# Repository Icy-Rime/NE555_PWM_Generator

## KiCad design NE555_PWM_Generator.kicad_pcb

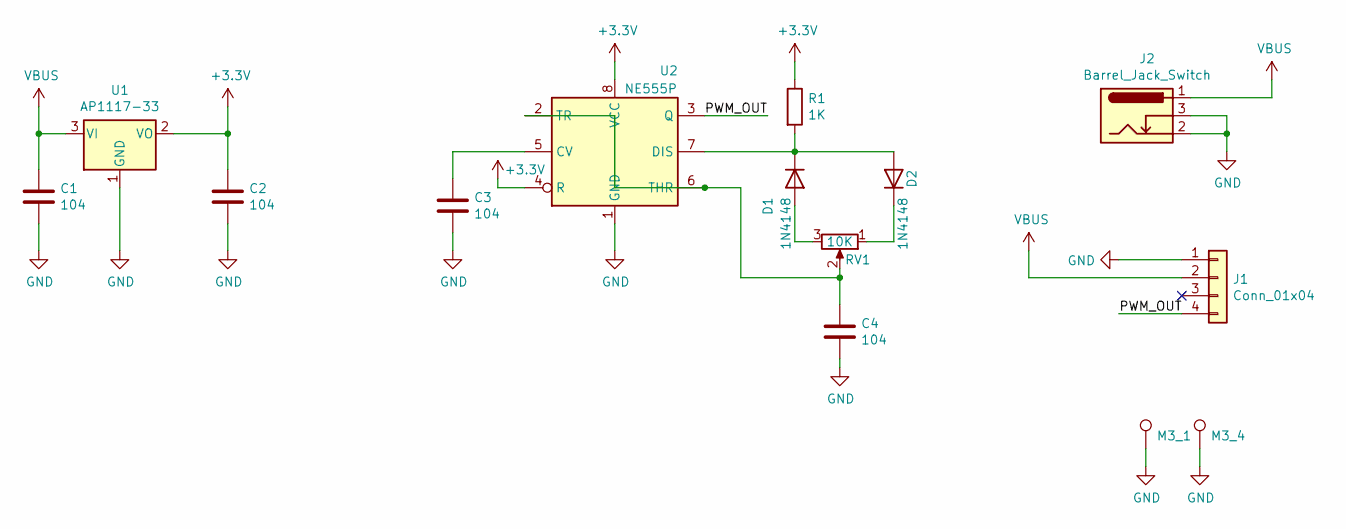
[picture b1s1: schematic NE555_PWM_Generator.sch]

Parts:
C1, C2, C3, C4: 104; R_0603_1608Metric
D1, D2: 1N4148; D_MiniMELF
J1: Conn_01x04; FanPinHeader_1x04_P2.54mm_Vertical
J2: Barrel_Jack_Switch; BarrelJack_Horizontal
M3_1, M3_4: TestPoint; MountingHole_2.2mm_M2_Pad_Via
R1: 1K; R_0603_1608Metric
RV1: 10K; Potentiometer_Bourns_3296W_Vertical
U1: AP1117-33; SOT-223-3_TabPin2
U2: NE555P; SOIC-8_3.9x4.9mm_P1.27mm

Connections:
+3V3: C2.1, R1.1, U1.2 (VO), U2.4 (R), U2.8 (VCC)
/PWM_OUT: J1.4, U2.3 (Q)
GND: C1.2, C2.2, C3.2, C4.2, J1.1, J2.2, J2.3, M3_1.1, M3_4.1, U1.1 (GND), U2.1 (GND)
unnamed: C3.1, U2.5 (CV)
unnamed: C4.1, RV1.2, U2.2 (TR), U2.6 (THR)
unnamed: D1.1 (K), D2.2 (A), R1.2, U2.7 (DIS)
unnamed: D1.2 (A), RV1.3
unnamed: D2.1 (K), RV1.1
VBUS: C1.1, J1.2, J2.1, U1.3 (VI)

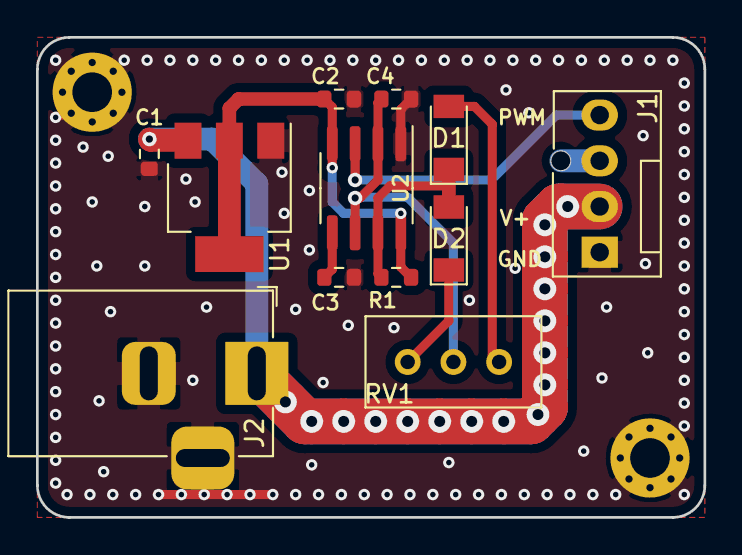
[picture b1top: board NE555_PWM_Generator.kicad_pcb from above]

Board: 2 copper layers, 37.1 x 26.7 mm, 14 parts (0 on the bottom side), 9 nets.

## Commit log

2021-03-17 First push
